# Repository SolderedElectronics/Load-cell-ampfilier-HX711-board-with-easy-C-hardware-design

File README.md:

# Load-cell ampfilier HX711 board with easyC Hardware design

## About the product

|  |
| :----------------------------------------------------------: |
|      [Buy Load-cell ampfilier HX711 board with easyC](https://www.solde.red/333006)      |

------ product description ------

## Repository contents

All Soldered Electronics hardware designed in KiCAD, and repositories are organized in the following way:

- CAD folder - contains KiCAD files (Schematics, Board, Panel Board), sorted by version. Change log lists all changes between versions.
- OUTPUTS - contains useful files, such as Bill of Materials (BOM), PDF of schematics, 3D .step file of the board and gerber files, sorted by version. 
- OUTPUTS -> Compliance - Certificates and useful legal stuff. 

## Want to contribute?

Please feel free to submit a pull request if you have any contributions. We encourage you to submit an issue or pull request if you find a bug. 

## About Soldered

At Soldered, we design and manufacture a wide selection of electronic products to help you turn your ideas into acts and bring you one step closer to your final project. Our products are intented for makers and crafted in-house by our experienced team in Osijek, Croatia. We believe that sharing is a crucial element for improvement and innovation, and we work hard to stay connected with all our makers regardless of their skill or experience level. Therefore, all our products are open-source. Finally, we always have your back. If you face any problem concerning either your shopping experience or your electronics project, our team will help you deal with it, offering efficient customer service and cost-free technical support anytime. Some of those might be useful for you:

- [Web Store](https://www.soldered.com/shop)
- [Tutorials & Projects](https://soldered.com/learn)
- [Community & Technical support](https://soldered.com/community)

## License info

All Soldered open-source hardware (OSH) is under The TAPR Open Hardware License. Read more in the LICENSE file. 

No warranty - all designs in this repository are distributed in the hope that they will be useful, but without any warranty. They are provided "AS IS", therefore without warranty of any kind, either expressed or implied. The entire quality and performance of what you do with the contents of this repository are your responsibility. In no event, Soldered Electronics will be liable for your damages, losses, including any general, special, incidental or consequential damage arising out of the use or inability to use the contents of this repository. 

## Have fun! 
And thank you from your fellow makers at Soldered Electronics.

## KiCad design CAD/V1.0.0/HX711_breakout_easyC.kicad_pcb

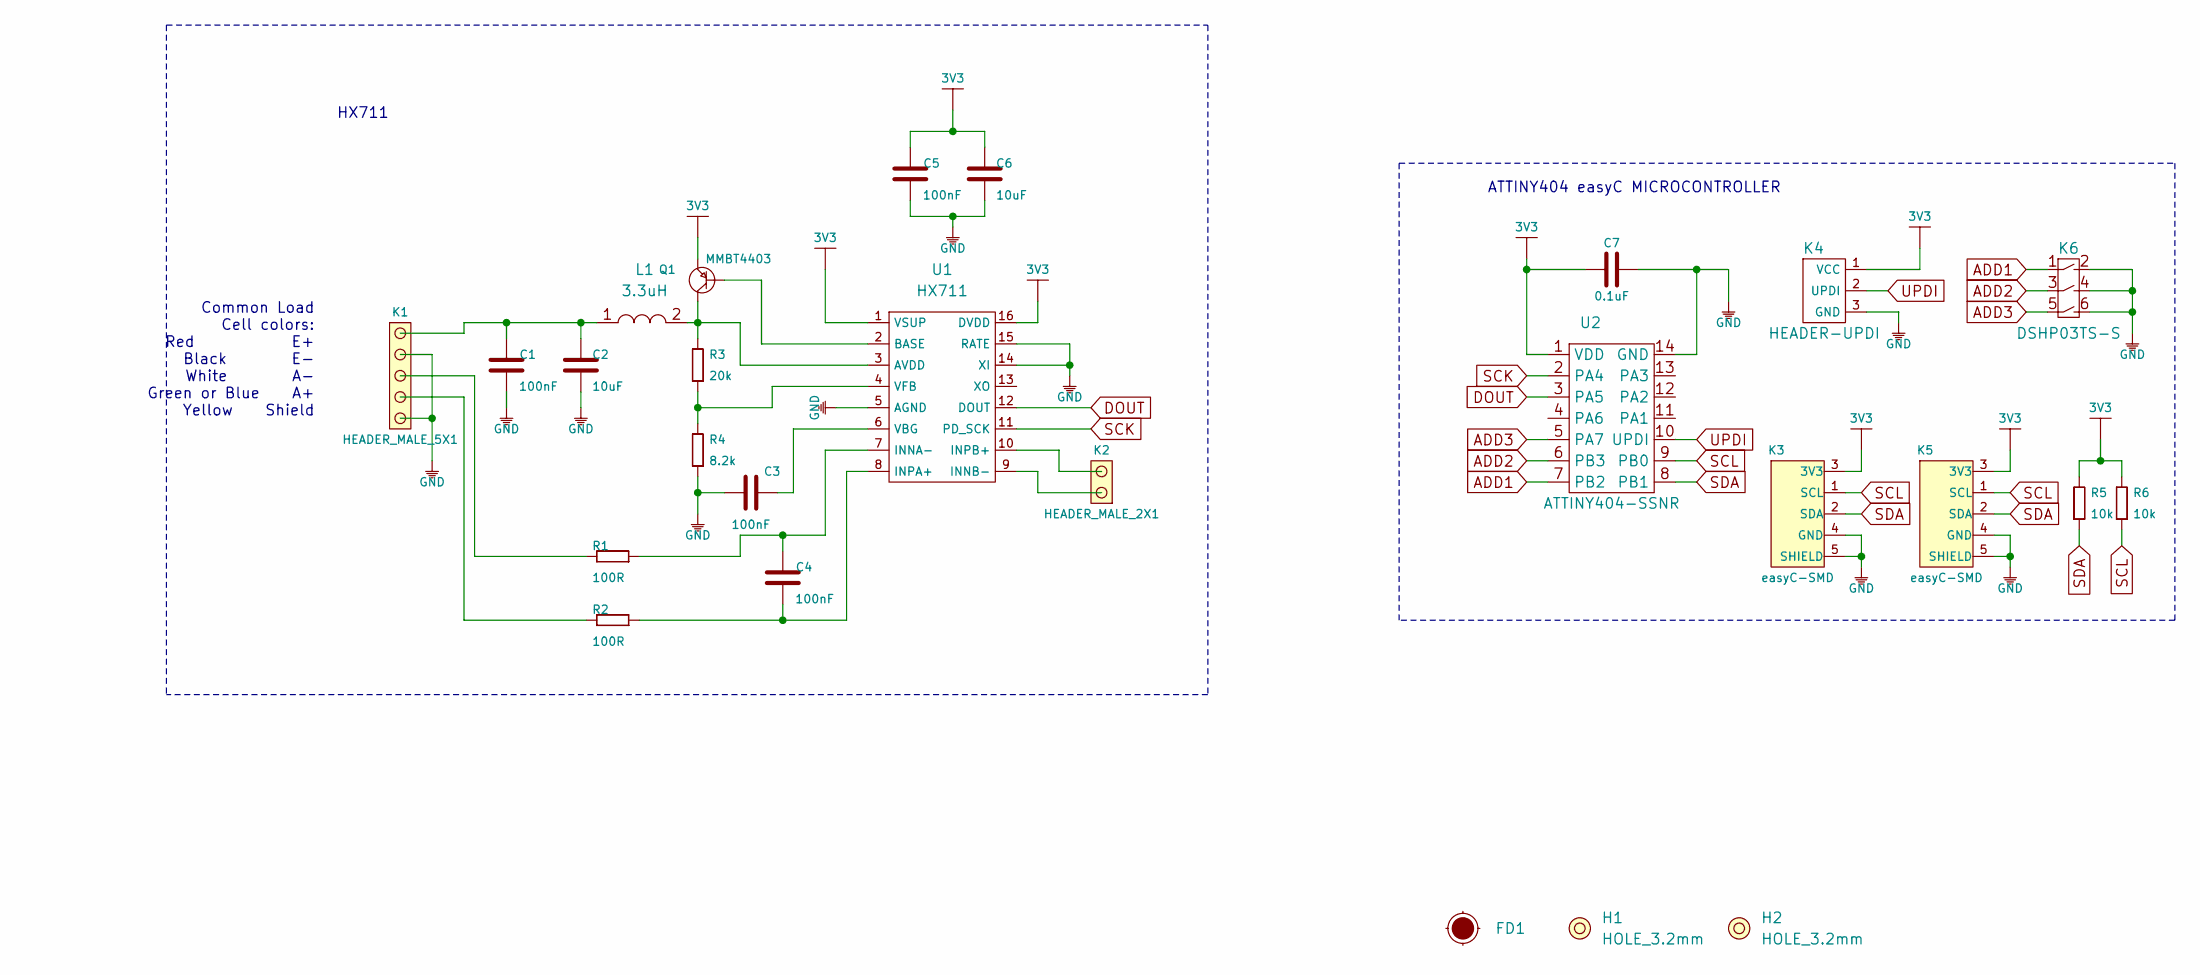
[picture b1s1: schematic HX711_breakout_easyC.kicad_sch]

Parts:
C1, C3, C4, C5: 100nF; 0603C
C2, C6: 10uF; 1206C
C7: 0.1uF; 0603C
FD1: Fiducial_Stencil; FIDUCIAL_1MM_PASTE
H1, H2: HOLE_3.2mm
K1: HEADER_MALE_5X1
K2: HEADER_MALE_2X1
K3, K5: easyC-SMD; easyC-connector
K4: HEADER-UPDI
K6: DSHP03TS-S
L1: 3.3uH; 0603L
Q1: MMBT4403; SOT-23-3
R1, R2: 100R; 0603R
R3: 20k; 0603R
R4: 8.2k; 0603R
R5, R6: 10k; 0603R
U1: HX711; SOP-16
U2: ATTINY404-SSNR; SOIC-14

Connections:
3V3: C5.2, C6.2, C7.1, K3.3 (3V3), K4.1 (VCC), K5.3 (3V3), Q1.2 (E), R5.2, R6.2, U1.1 (VSUP), U1.16 (DVDD), U2.1 (VDD)
ADD1: K6.1, U2.7 (PB2)
ADD2: K6.3, U2.6 (PB3)
ADD3: K6.5, U2.5 (PA7)
DOUT: U1.12 (DOUT), U2.3 (PA5)
GND: C1.1, C2.1, C3.1, C5.1, C6.1, C7.2, K1.1, K1.4, K3.4 (GND), K3.5 (SHIELD), K4.3 (GND), K5.4 (GND), K5.5 (SHIELD), K6.2, K6.4, K6.6, R4.1, U1.5 (AGND), U1.14 (XI), U1.15 (RATE), U2.14 (GND)
unnamed: C1.2, C2.2, K1.5, L1.1
unnamed: C3.2, U1.6 (VBG)
unnamed: C4.1, R2.1, U1.8 (INPA+)
unnamed: C4.2, R1.1, U1.7 (INNA-)
unnamed: K1.2, R2.2
unnamed: K1.3, R1.2
unnamed: K2.1, U1.9 (INNB-)
unnamed: K2.2, U1.10 (INPB+)
unnamed: L1.2, Q1.3 (C), R3.2, U1.3 (AVDD)
unnamed: Q1.1 (B), U1.2 (BASE)
unnamed: R3.1, R4.2, U1.4 (VFB)
SCK: U1.11 (PD_SCK), U2.2 (PA4)
SCL: K3.1 (SCL), K5.1 (SCL), R6.1, U2.9 (PB0)
SDA: K3.2 (SDA), K5.2 (SDA), R5.1, U2.8 (PB1)
UPDI: K4.2 (UPDI), U2.10 (UPDI)

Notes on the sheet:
Common Load Cell colors: Red E+ Black E- White A- Green or Blue A+ Yellow Shield
HX711
ATTINY404 easyC MICROCONTROLLER

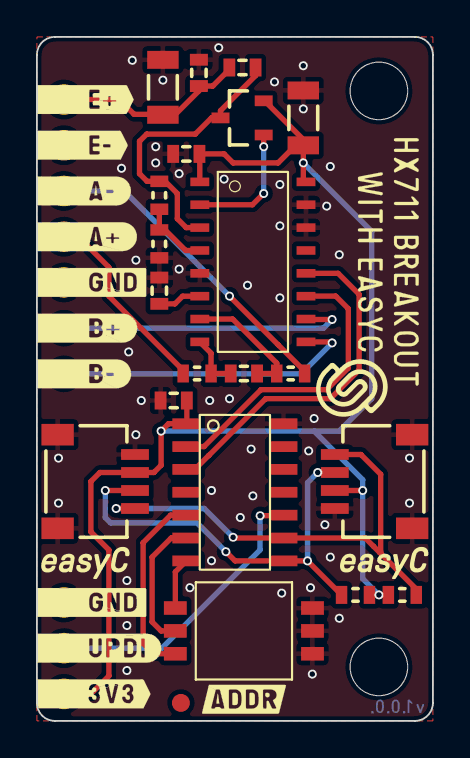
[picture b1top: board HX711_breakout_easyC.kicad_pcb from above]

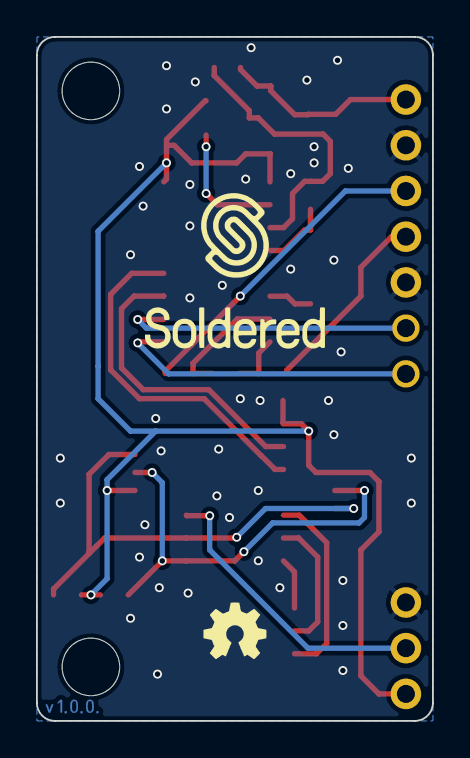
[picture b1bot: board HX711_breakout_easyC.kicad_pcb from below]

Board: 2 copper layers, 22.0 x 38.0 mm, 26 parts (2 on the bottom side), 21 nets.

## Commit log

2022-08-06 Updating open source files.
